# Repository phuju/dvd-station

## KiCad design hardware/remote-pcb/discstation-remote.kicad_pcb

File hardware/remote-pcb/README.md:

# DiscStation Remote PCB (r1)

One 72 × 64 mm, 2-layer board that replaces the module-based remote. It has the
same outline, mounting holes and front-panel layout as the EasyEDA carrier board.
The GPIOs are unchanged, so the firmware and host need no changes. The design notes
are in [`docs/PCB.md`](../../docs/PCB.md).

| File | What it is |
|---|---|
| `discstation-remote-schematic.pdf` | Schematic, for review |
| `discstation-remote-gerbers.zip` | Gerbers + drill files to upload to JLCPCB |
| `fab/discstation-remote-bom.csv` | Bill of materials |
| `fab/discstation-remote-pos.csv` | Pick-and-place positions (top and bottom) |
| `preview-top.png`, `preview-bottom.png` | 3D renders |
| `discstation-remote.kicad_pro/.kicad_sch/.kicad_pcb` | KiCad 10 project |

- **Front:** PLAY, HOME and EJECT Cherry MX-style key switches (3- or 5-pin), the EC11 encoder, a 4-pin OLED
  header with 4 M2 standoff holes, the power and charge LEDs.
- **Back:** ESP32-WROOM-32E (antenna on the right edge, no copper under it),
  CP2102N with DevKit-style auto-program, MCP73831 charger with a power path,
  AP2112K 3.3 V regulator, USB-C and power switch on the bottom edge, JST-PH battery
  connector (bottom-left), RESET and BOOT buttons, and the always-on eye LED (D4,
  XL-1608UBC-04) at (55.6, 58.4) mm. The 22 × 13 mm area around D4 is kept free for the
  eye/logo silkscreen art; import it with KiCad's Image Converter onto B.Silkscreen.
- LEDs are XL-1608UBC-04 (0603 blue): D2 power and D3 charging on the front, D4 eye on the back.

## Art and test pads

- **Front:** the disc sketch and "DISCSTATION" in the Phuju font, bottom-right.
- **Back:** the eye sketch, with its pupil on the eye LED (D4).
- **Test pads:** TP1 is a heart-shaped GND pad at (32.5, 9.0) mm and TP2 is a round 3V3
  pad at (69.0, 54.0) mm. Both have a 1 mm plated hole, so the pad is on both sides.

The sketches and text are converted to silkscreen polygons, so the font doesn't need to
be installed. Each piece of art is a group, so you can move it in KiCad as one unit.
The test-pad footprints are in the project library `discstation.pretty`.
To redo the art: `python3 art/prep_art.py`, then
`flatpak run --command=python3 org.kicad.KiCad art/add_art.py` on a board that has
no art yet.

## Editing

From r1 on, the KiCad files are edited by hand in KiCad 10: open
`discstation-remote.kicad_pro`. After editing, rerun DRC and export new Gerbers
from KiCad's Plot dialog, or run `./build.sh fab`, which regenerates the fab files
without touching the design.

**Do not run the full `./build.sh` after hand edits.** It regenerates the schematic
and board from `design.py` and overwrites them. The note in the schematic's title
block ("edit design.py") comes from that generator and no longer applies.

## Regenerating from scratch (generator, as used for r1)

```bash
FREEROUTING=/path/to/freerouting-1.9.0.jar ./build.sh
```

This runs the steps in order and stops at the first failure: firmware pin check →
schematic → ERC → netlist → placement (`gen_pcb.py`) → Freerouting (about 25 minutes)
→ ground pours → DRC with schematic parity → Gerbers, drill, BOM and positions.
`./build.sh fab` reruns only DRC and the fabrication outputs.

## State of r1

- ERC: 0 violations. DRC: 0 errors, 0 unconnected, 0 schematic-parity issues.
- Remaining warnings are silkscreen only (labels near the edge connectors, and labels
  over pads, which the fab house clips). The ESP32 footprint is reported as modified
  on purpose: see below.

## Review before ordering

- **Autorouted.** Check the USB D+/D− pair, the power traces and the ground pours.
- **Antenna keep-out:** Espressif's full keep-out (48 × 21 mm) does not fit on this
  board. Only the area under the antenna is kept clear, which is a common compromise
  on small boards. Wi-Fi range may be somewhat shorter than on the DevKit.
- **Positions come from a screenshot** of the old board (±1 mm). The encoder position
  is a guess, because the old board used a module with a header. Check every control
  against the enclosure, and allow for the USB-C port and power switch on the bottom
  edge (the switch lever sticks out about 0.5 mm).
- **Battery polarity:** pin 1 of J3 is `+`, but JST-PH battery leads are not wired
  the same way by every seller. Check before plugging one in.
- **Keycap clearance:** the keys keep your EasyEDA layout's spacing (about 18.4 mm
  between centres, against the usual 19.05 mm). Standard 1u keycaps (about 18 mm wide)
  leave only ~0.4 mm between them, so check that yours don't rub.
- **Encoder direction:** if turning the knob scrolls the wrong way, swap
  `ENC_CLK_PIN` and `ENC_DT_PIN` in the firmware.
- **The BOM has no LCSC part numbers.** Choose them when you upload to JLCPCB. Have
  the surface-mount parts (back side) assembled and hand-solder the through-hole parts.

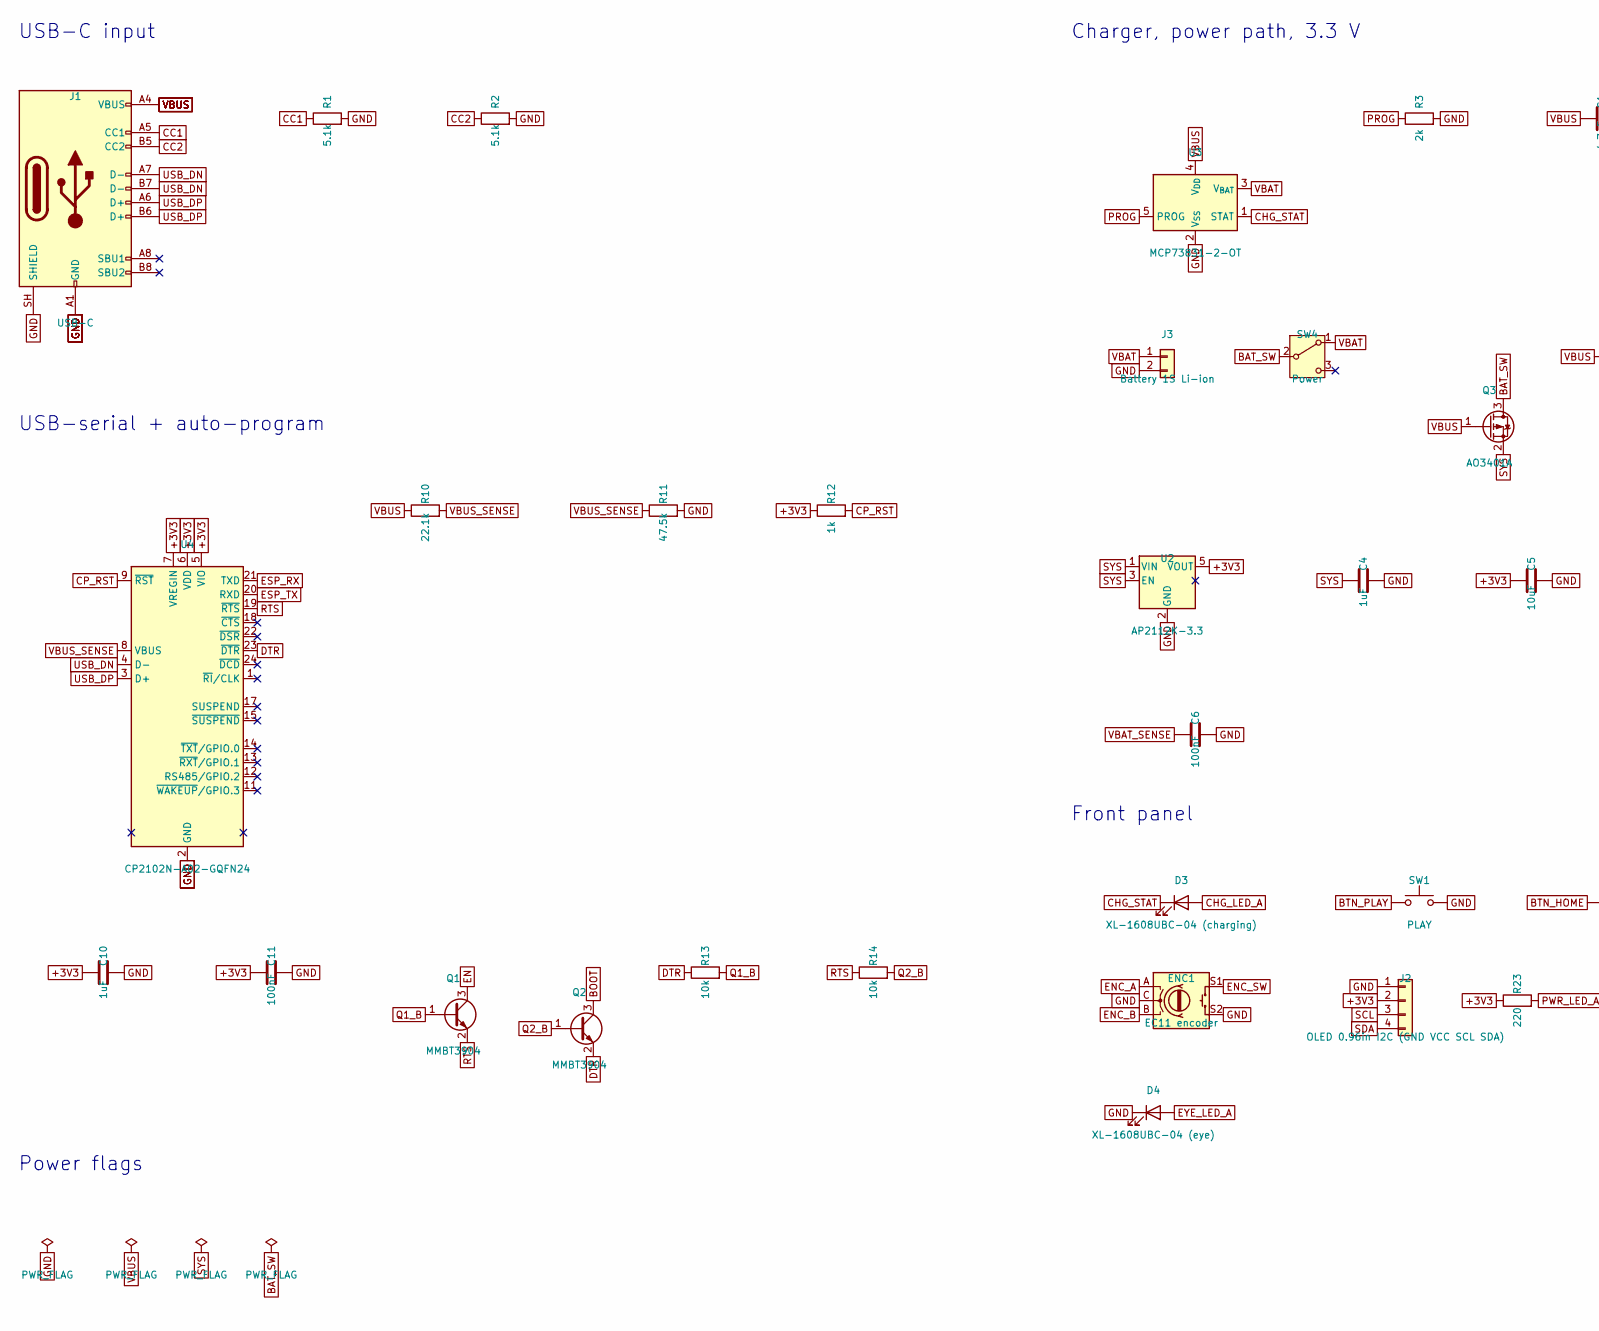
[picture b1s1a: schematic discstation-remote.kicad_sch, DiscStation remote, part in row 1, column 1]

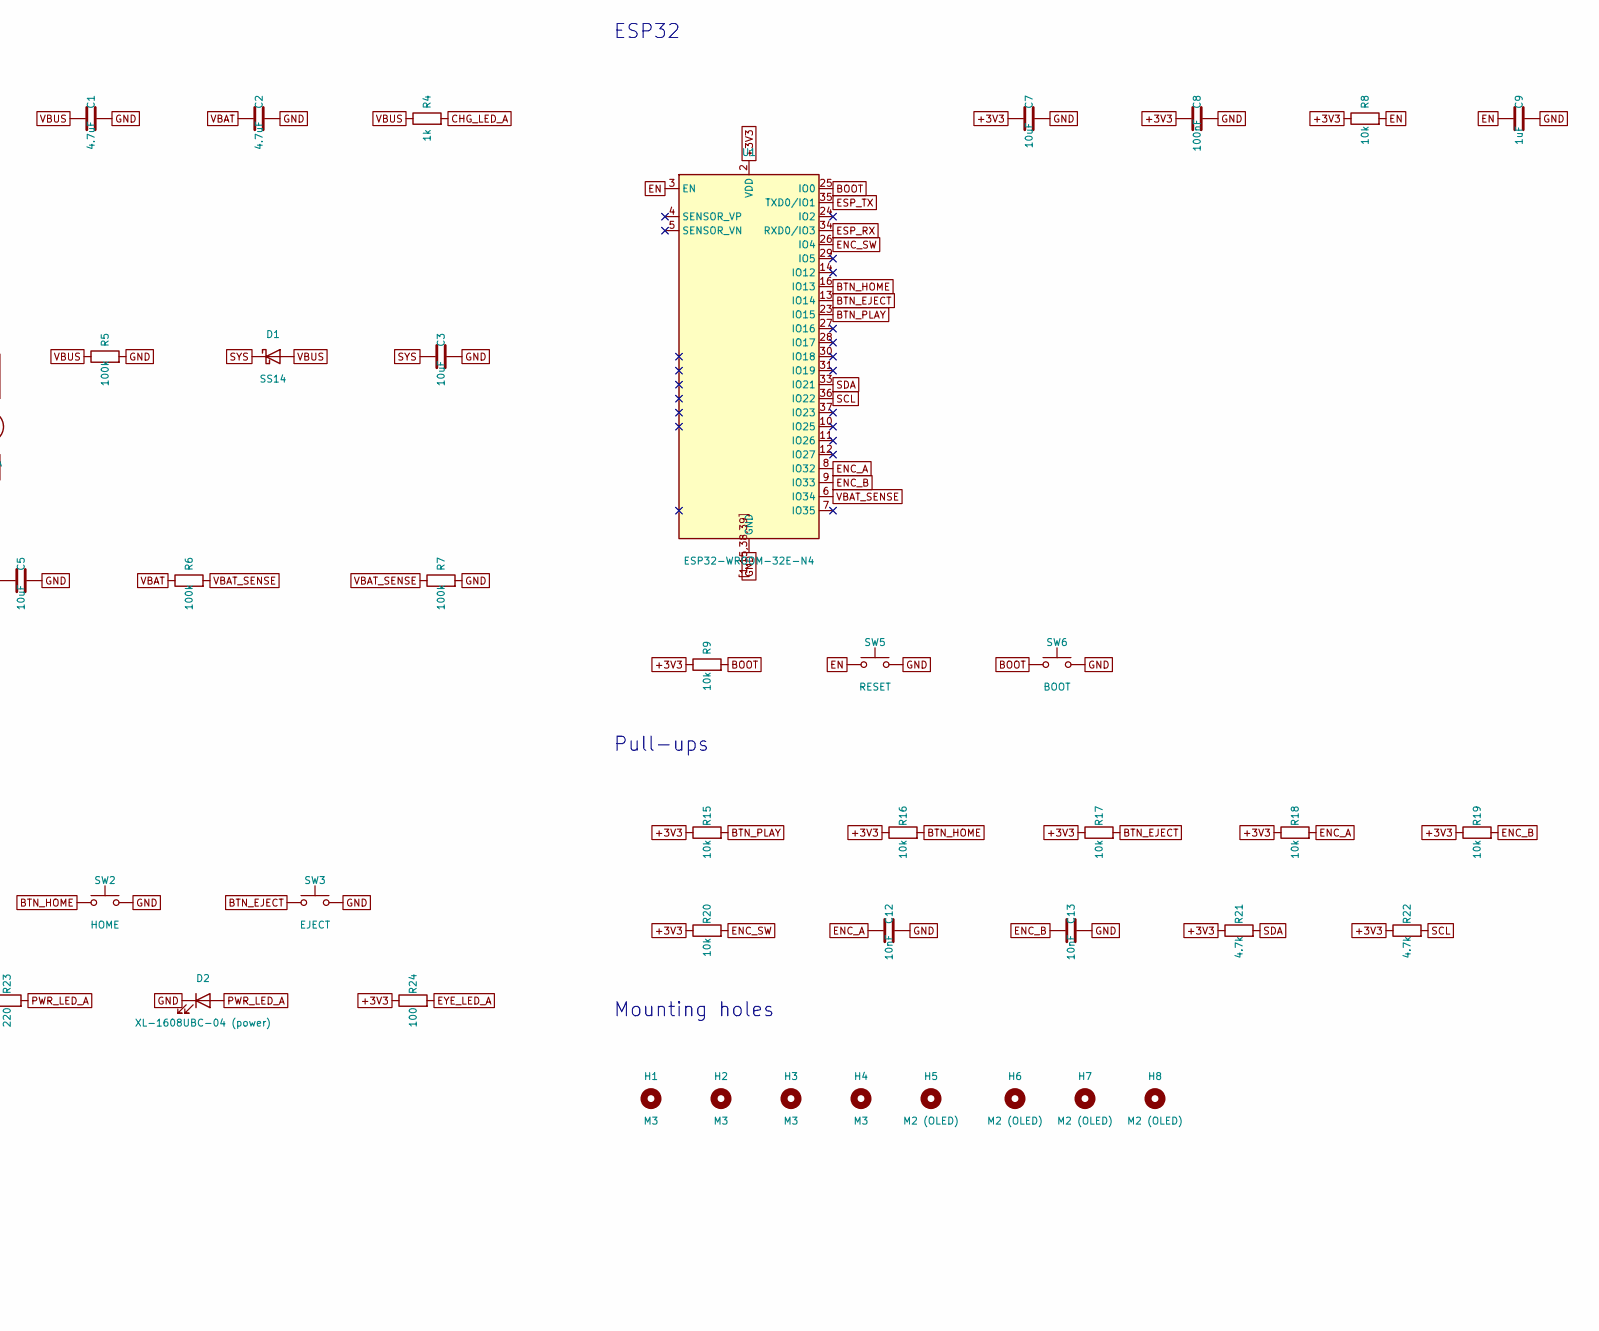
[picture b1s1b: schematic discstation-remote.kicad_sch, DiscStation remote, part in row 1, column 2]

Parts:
C1, C2: 4.7uF; C_0805_2012Metric
C3, C5, C7: 10uF; C_0805_2012Metric
C4, C9, C10: 1uF; C_0603_1608Metric
C6, C8, C11: 100nF; C_0603_1608Metric
C12, C13: 10nF; C_0603_1608Metric
D1: SS14; D_SMA
D2: XL-1608UBC-04 (power); LED_0603_1608Metric
D3: XL-1608UBC-04 (charging); LED_0603_1608Metric
D4: XL-1608UBC-04 (eye); LED_0603_1608Metric
ENC1: EC11 encoder; RotaryEncoder_Alps_EC11E-Switch_Vertical_H20mm
H1, H2, H3, H4: M3; MountingHole_3.2mm_M3
H5, H6, H7, H8: M2 (OLED); MountingHole_2.2mm_M2
J1: USB-C; USB_C_Receptacle_HRO_TYPE-C-31-M-12
J2: OLED 0.96in I2C (GND VCC SCL SDA); PinHeader_1x04_P2.54mm_Vertical
J3: Battery 1S Li-ion; JST_PH_B2B-PH-K_1x02_P2.00mm_Vertical
Q1, Q2: MMBT3904; SOT-23
Q3: AO3401A; SOT-23
R1, R2: 5.1k; R_0603_1608Metric
R3: 2k; R_0603_1608Metric
R4, R12: 1k; R_0603_1608Metric
R5, R6, R7: 100k; R_0603_1608Metric
R8, R9, R13, R14, R15, R16, R17, R18, R19, R20: 10k; R_0603_1608Metric
R10: 22.1k; R_0603_1608Metric
R11: 47.5k; R_0603_1608Metric
R21, R22: 4.7k; R_0603_1608Metric
R23: 220; R_0603_1608Metric
R24: 100; R_0603_1608Metric
SW1: PLAY; SW_Cherry_MX_1.00u_PCB
SW2: HOME; SW_Cherry_MX_1.00u_PCB
SW3: EJECT; SW_Cherry_MX_1.00u_PCB
SW4: Power; SW_SPDT_PCM12
SW5: RESET; SW_SPST_TL3342
SW6: BOOT; SW_SPST_TL3342
U1: ESP32-WROOM-32E-N4; ESP32-WROOM-32E
U2: AP2112K-3.3; SOT-23-5
U3: MCP73831-2-OT; SOT-23-5
U4: CP2102N-A02-GQFN24; QFN-24-1EP_4x4mm_P0.5mm_EP2.6x2.6mm

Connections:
+3V3: C5.1, C7.1, C8.1, C10.1, C11.1, J2.2, R8.1, R9.1, R12.1, R15.1, R16.1, R17.1, R18.1, R19.1, R20.1, R21.1, R22.1, R23.1, R24.1, U1.2 (VDD), U2.5 (VOUT), U4.5 (VIO), U4.6 (VDD), U4.7 (VREGIN); also elsewhere on the board
BAT_SW: Q3.3 (D), SW4.2 (B)
BOOT: Q2.3 (C), R9.2, SW6.1, U1.25 (IO0)
BTN_EJECT: R17.2, SW3.1, U1.13 (IO14)
BTN_HOME: R16.2, SW2.1, U1.16 (IO13)
BTN_PLAY: R15.2, SW1.1, U1.23 (IO15)
CC1: J1.A5 (CC1), R1.1
CC2: J1.B5 (CC2), R2.1
CHG_LED_A: D3.2 (A), R4.2
CHG_STAT: D3.1 (K), U3.1 (STAT)
CP_RST: R12.2, U4.9 (~RST)
DTR: Q2.2 (E), R13.1, U4.23 (~DTR)
EN: C9.1, Q1.3 (C), R8.2, SW5.1, U1.3 (EN)
ENC_A: C12.1, ENC1.A, R18.2, U1.8 (IO32)
ENC_B: C13.1, ENC1.B, R19.2, U1.9 (IO33)
ENC_SW: ENC1.S1, R20.2, U1.26 (IO4)
ESP_RX: U1.34 (RXD0/IO3), U4.21 (TXD)
ESP_TX: U1.35 (TXD0/IO1), U4.20 (RXD)
EYE_LED_A: D4.2 (A), R24.2
GND: C1.2, C2.2, C3.2, C4.2, C5.2, C6.2, C7.2, C8.2, C9.2, C10.2, C11.2, C12.2, C13.2, D2.1 (K), D4.1 (K), ENC1.C, ENC1.S2, J1.A1 (GND), J1.A12 (GND), J1.B1 (GND), J1.B12 (GND), J1.SH (SHIELD), J2.1, J3.2, R1.2, R2.2, R3.2, R5.2, R7.2, R11.2, SW1.2, SW2.2, SW3.2, SW5.2, SW6.2, U1.1, U1.15, U1.38, U1.39, U1.[1,15,38,39] (GND), U2.2 (GND), U3.2 (V_{SS}), U4.2 (GND), U4.25 (GND); also elsewhere on the board
PROG: R3.1, U3.5 (PROG)
PWR_LED_A: D2.2 (A), R23.2
Q1_B: Q1.1 (B), R13.2
Q2_B: Q2.1 (B), R14.2
RTS: Q1.2 (E), R14.1, U4.19 (~RTS)
SCL: J2.3, R22.2, U1.36 (IO22)
SDA: J2.4, R21.2, U1.33 (IO21)
SYS: C3.1, C4.1, D1.1 (K), Q3.2 (S), U2.1 (VIN), U2.3 (EN)
USB_DN: J1.A7 (D-), J1.B7 (D-), U4.4 (D-)
USB_DP: J1.A6 (D+), J1.B6 (D+), U4.3 (D+)
VBAT: C2.1, J3.1, R6.1, SW4.1 (A), U3.3 (V_{BAT})
VBAT_SENSE: C6.1, R6.2, R7.1, U1.6 (IO34)
VBUS: C1.1, D1.2 (A), J1.A4 (VBUS), J1.A9 (VBUS), J1.B4 (VBUS), J1.B9 (VBUS), Q3.1 (G), R4.1, R5.1, R10.1, U3.4 (V_{DD})
VBUS_SENSE: R10.2, R11.1, U4.8 (VBUS)

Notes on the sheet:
USB-C input
Charger, power path, 3.3 V
ESP32
USB-serial + auto-program
Pull-ups
Front panel
Mounting holes
Power flags

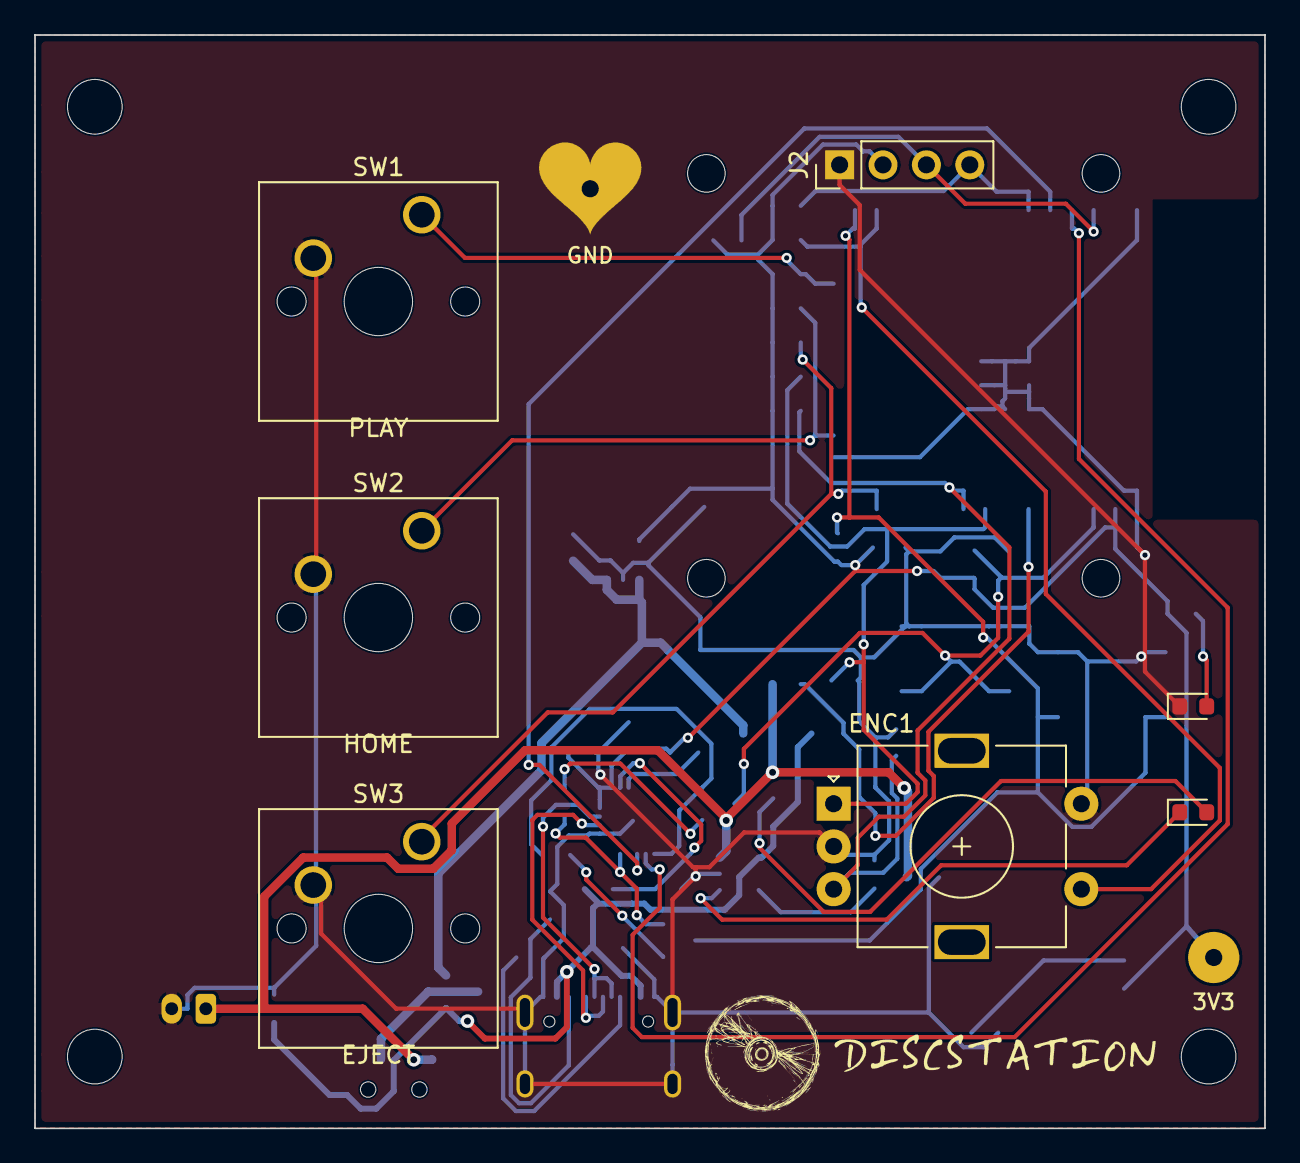
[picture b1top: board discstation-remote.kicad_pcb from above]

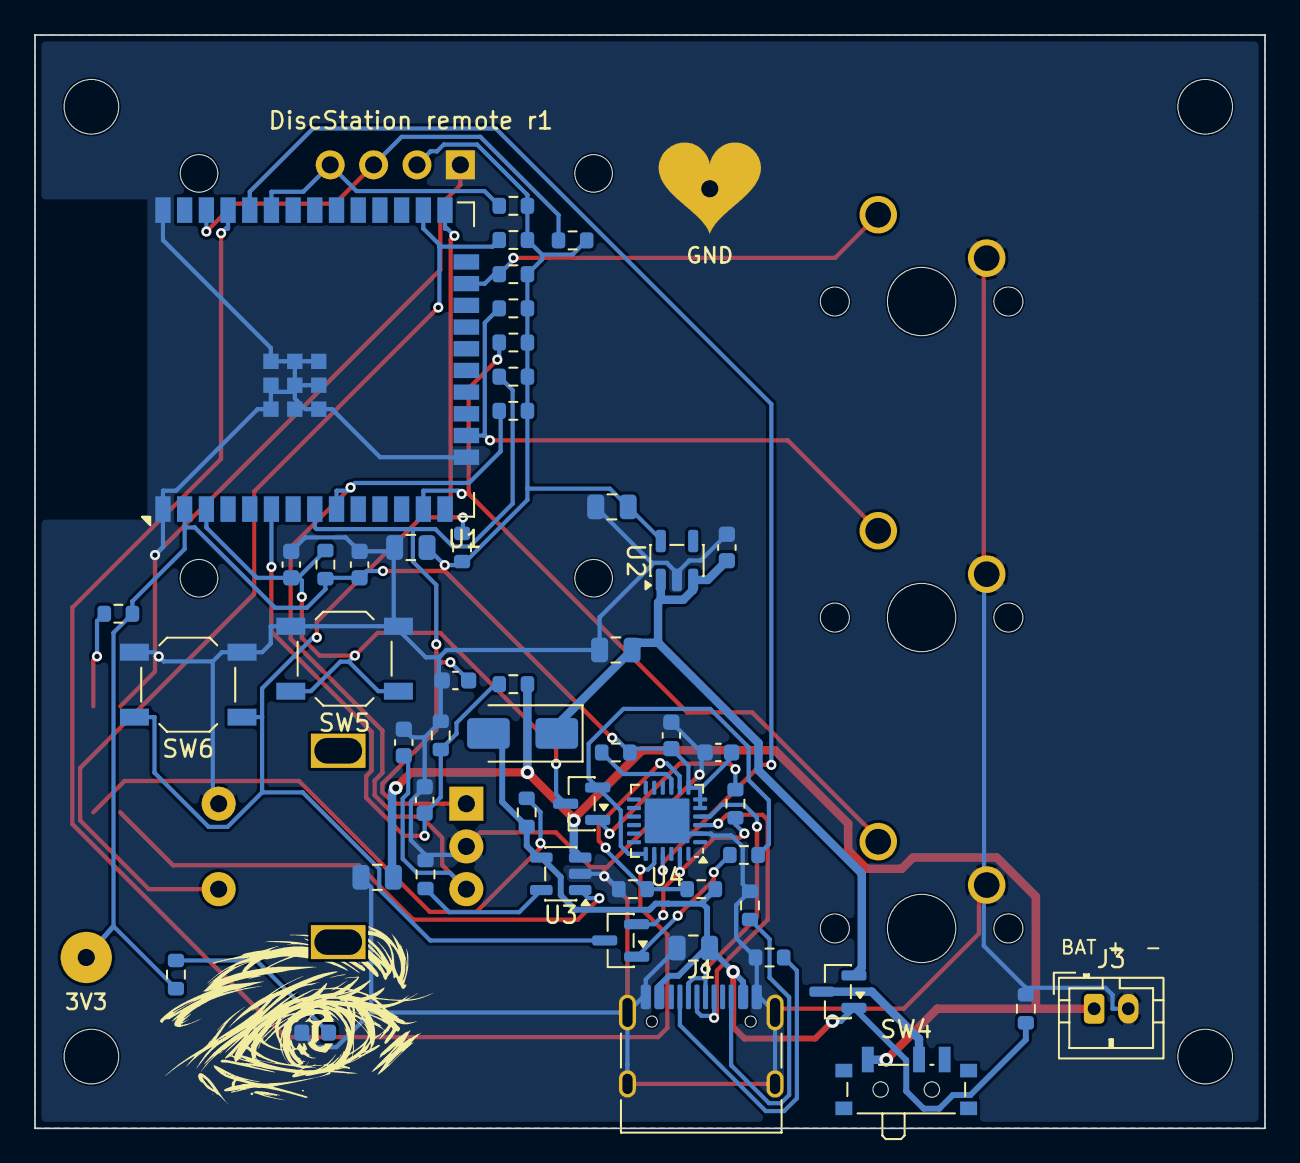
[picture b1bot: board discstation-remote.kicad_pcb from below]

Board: 2 copper layers, 72.0 x 64.0 mm, 68 parts (51 on the bottom side), 34 nets.

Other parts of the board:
TP1: GND; TestPad_Heart
TP2: +3V3; TestPad_Round

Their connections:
+3V3: TP2.1; also elsewhere on the board
GND: TP1.1; also elsewhere on the board

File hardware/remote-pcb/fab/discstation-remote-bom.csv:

"Designator","Value","Footprint","Qty"
"C1,C2","4.7uF","Capacitor_SMD:C_0805_2012Metric","2"
"C3,C5,C7","10uF","Capacitor_SMD:C_0805_2012Metric","3"
"C4,C9,C10","1uF","Capacitor_SMD:C_0603_1608Metric","3"
"C6,C8,C11","100nF","Capacitor_SMD:C_0603_1608Metric","3"
"C12,C13","10nF","Capacitor_SMD:C_0603_1608Metric","2"
"D1","SS14","Diode_SMD:D_SMA","1"
"D2","XL-1608UBC-04 (power)","LED_SMD:LED_0603_1608Metric","1"
"D3","XL-1608UBC-04 (charging)","LED_SMD:LED_0603_1608Metric","1"
"D4","XL-1608UBC-04 (eye)","LED_SMD:LED_0603_1608Metric","1"
"ENC1","EC11 encoder","Rotary_Encoder:RotaryEncoder_Alps_EC11E-Switch_Vertical_H20mm","1"
"J1","USB-C","Connector_USB:USB_C_Receptacle_HRO_TYPE-C-31-M-12","1"
"J2","OLED 0.96in I2C (GND VCC SCL SDA)","Connector_PinHeader_2.54mm:PinHeader_1x04_P2.54mm_Vertical","1"
"J3","Battery 1S Li-ion","Connector_JST:JST_PH_B2B-PH-K_1x02_P2.00mm_Vertical","1"
"Q1,Q2","MMBT3904","Package_TO_SOT_SMD:SOT-23","2"
"Q3","AO3401A","Package_TO_SOT_SMD:SOT-23","1"
"R1,R2","5.1k","Resistor_SMD:R_0603_1608Metric","2"
"R3","2k","Resistor_SMD:R_0603_1608Metric","1"
"R4,R12","1k","Resistor_SMD:R_0603_1608Metric","2"
"R5-R7","100k","Resistor_SMD:R_0603_1608Metric","3"
"R8,R9,R13-R20","10k","Resistor_SMD:R_0603_1608Metric","10"
"R10","22.1k","Resistor_SMD:R_0603_1608Metric","1"
"R11","47.5k","Resistor_SMD:R_0603_1608Metric","1"
"R21,R22","4.7k","Resistor_SMD:R_0603_1608Metric","2"
"R23","220","Resistor_SMD:R_0603_1608Metric","1"
"R24","100","Resistor_SMD:R_0603_1608Metric","1"
"SW1","PLAY","Button_Switch_Keyboard:SW_Cherry_MX_1.00u_PCB","1"
"SW2","HOME","Button_Switch_Keyboard:SW_Cherry_MX_1.00u_PCB","1"
"SW3","EJECT","Button_Switch_Keyboard:SW_Cherry_MX_1.00u_PCB","1"
"SW4","Power","Button_Switch_SMD:SW_SPDT_PCM12","1"
"SW5","RESET","Button_Switch_SMD:SW_SPST_TL3342","1"
"SW6","BOOT","Button_Switch_SMD:SW_SPST_TL3342","1"
"U1","ESP32-WROOM-32E-N4","RF_Module:ESP32-WROOM-32E","1"
"U2","AP2112K-3.3","Package_TO_SOT_SMD:SOT-23-5","1"
"U3","MCP73831-2-OT","Package_TO_SOT_SMD:SOT-23-5","1"
"U4","CP2102N-A02-GQFN24","Package_DFN_QFN:QFN-24-1EP_4x4mm_P0.5mm_EP2.6x2.6mm","1"

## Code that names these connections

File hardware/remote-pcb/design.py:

"""DiscStation remote: the one source of truth for the schematic and the PCB.

GPIOs match arduino/DiscStation/DiscStation.ino exactly (no firmware change).
Each part: ref -> (lib_id, value, footprint, {symbol pin number: net}, block).
Unlisted pins of a part are no-connects.
"""

R0603 = "Resistor_SMD:R_0603_1608Metric"
C0603 = "Capacitor_SMD:C_0603_1608Metric"
C0805 = "Capacitor_SMD:C_0805_2012Metric"
SOT23 = "Package_TO_SOT_SMD:SOT-23"
SOT235 = "Package_TO_SOT_SMD:SOT-23-5"

PARTS = {}


def part(ref, lib_id, value, fp, pins, block):
    assert ref not in PARTS, ref
    PARTS[ref] = (lib_id, value, fp, pins, block)


def R(ref, value, a, b, block):
    part(ref, "Device:R", value, R0603, {"1": a, "2": b}, block)


def C(ref, value, a, b, block, fp=C0603):
    part(ref, "Device:C", value, fp, {"1": a, "2": b}, block)


# ---- USB-C input -------------------------------------------------------------
USB_VBUS = ["A4", "A9", "B4", "B9"]
USB_GND = ["A1", "B1", "A12", "B12", "SH"]
part("J1", "Connector:USB_C_Receptacle_USB2.0_16P", "USB-C", "Connector_USB:USB_C_Receptacle_HRO_TYPE-C-31-M-12",
     {**{p: "VBUS" for p in USB_VBUS}, **{p: "GND" for p in USB_GND},
      "A5": "CC1", "B5": "CC2", "A6": "USB_DP", "B6": "USB_DP", "A7": "USB_DN", "B7": "USB_DN"}, "usb")
R("R1", "5.1k", "CC1", "GND", "usb")
R("R2", "5.1k", "CC2", "GND", "usb")

# ---- Li-ion charger + power path ------------------------------------------------
part("U3", "Battery_Management:MCP73831-2-OT", "MCP73831-2-OT", SOT235,
     {"1": "CHG_STAT", "2": "GND", "3": "VBAT", "4": "VBUS", "5": "PROG"}, "power")
R("R3", "2k", "PROG", "GND", "power")                # charge current 1000/2k = 500 mA
C("C1", "4.7uF", "VBUS", "GND", "power", C0805)
C("C2", "4.7uF", "VBAT", "GND", "power", C0805)
R("R4", "1k", "VBUS", "CHG_LED_A", "power")
part("D3", "Device:LED", "XL-1608UBC-04 (charging)", "LED_SMD:LED_0603_1608Metric", {"1": "CHG_STAT", "2": "CHG_LED_A"}, "front")
part("J3", "Connector_Generic:Conn_01x02", "Battery 1S Li-ion", "Connector_JST:JST_PH_B2B-PH-K_1x02_P2.00mm_Vertical",
     {"1": "VBAT", "2": "GND"}, "power")
part("SW4", "Switch:SW_SPDT", "Power", "Button_Switch_SMD:SW_SPDT_PCM12",
     {"1": "VBAT", "2": "BAT_SW"}, "power")
# USB present: gate high, P-FET off, load runs from VBUS via D1. USB absent:
# R5 pulls the gate low and the battery feeds SYS through the FET.
part("Q3", "Transistor_FET:AO3401A", "AO3401A", SOT23, {"1": "VBUS", "2": "SYS", "3": "BAT_SW"}, "power")
R("R5", "100k", "VBUS", "GND", "power")
part("D1", "Diode:SS14", "SS14", "Diode_SMD:D_SMA", {"1": "SYS", "2": "VBUS"}, "power")
C("C3", "10uF", "SYS", "GND", "power", C0805)

# ---- 3.3 V regulator ---------------------------------------------------------
part("U2", "Regulator_Linear:AP2112K-3.3", "AP2112K-3.3", SOT235,
     {"1": "SYS", "2": "GND", "3": "SYS", "5": "+3V3"}, "power")
C("C4", "1uF", "SYS", "GND", "power")
C("C5", "10uF", "+3V3", "GND", "power", C0805)

# battery gauge for later firmware use (GPIO34, ADC1)
R("R6", "100k", "VBAT", "VBAT_SENSE", "power")
R("R7", "100k", "VBAT_SENSE", "GND", "power")
C("C6", "100nF", "VBAT_SENSE", "GND", "power")

# ---- ESP32 ---------------------------------------------------------------------
part("U1", "RF_Module:ESP32-WROOM-32E", "ESP32-WROOM-32E-N4", "RF_Module:ESP32-WROOM-32E",
     {"[1,15,38,39]": "GND", "2": "+3V3", "3": "EN", "25": "BOOT",
      "26": "ENC_SW",       # IO4
      "16": "BTN_HOME",     # IO13
      "13": "BTN_EJECT",    # IO14
      "23": "BTN_PLAY",     # IO15 (strapping pin, idles high)
      "33": "SDA",          # IO21
      "36": "SCL",          # IO22
      "8": "ENC_A",         # IO32
      "9": "ENC_B",         # IO33
      "6": "VBAT_SENSE",    # IO34
      "35": "ESP_TX", "34": "ESP_RX"}, "mcu")
C("C7", "10uF", "+3V3", "GND", "mcu", C0805)
C("C8", "100nF", "+3V3", "GND", "mcu")
R("R8", "10k", "+3V3", "EN", "mcu")
C("C9", "1uF", "EN", "GND", "mcu")
R("R9", "10k", "+3V3", "BOOT", "mcu")
part("SW5", "Switch:SW_Push", "RESET", "Button_Switch_SMD:SW_SPST_TL3342", {"1": "EN", "2": "GND"}, "mcu")
part("SW6", "Switch:SW_Push", "BOOT", "Button_Switch_SMD:SW_SPST_TL3342", {"1": "BOOT", "2": "GND"}, "mcu")

# ---- USB-serial (CP2102N, self-powered from 3V3; VBUS sensed via divider) --------
part("U4", "Interface_USB:CP2102N-Axx-xQFN24", "CP2102N-A02-GQFN24", "Package_DFN_QFN:QFN-24-1EP_4x4mm_P0.5mm_EP2.6x2.6mm",
     {"2": "GND", "25": "GND", "3": "USB_DP", "4": "USB_DN", "5": "+3V3", "6": "+3V3", "7": "+3V3",
      "8": "VBUS_SENSE", "9": "CP_RST", "20": "ESP_TX", "21": "ESP_RX", "19": "RTS", "23": "DTR"}, "usbserial")
R("R10", "22.1k", "VBUS", "VBUS_SENSE", "usbserial")
R("R11", "47.5k", "VBUS_SENSE", "GND", "usbserial")
R("R12", "1k", "+3V3", "CP_RST", "usbserial")
C("C10", "1uF", "+3V3", "GND", "usbserial")
C("C11", "100nF", "+3V3", "GND", "usbserial")
# auto-program (same as the DevKit): DTR/RTS drive EN and IO0
part("Q1", "Transistor_BJT:MMBT3904", "MMBT3904", SOT23, {"1": "Q1_B", "2": "RTS", "3": "EN"}, "usbserial")
part("Q2", "Transistor_BJT:MMBT3904", "MMBT3904", SOT23, {"1": "Q2_B", "2": "DTR", "3": "BOOT"}, "usbserial")
R("R13", "10k", "DTR", "Q1_B", "usbserial")
R("R14", "10k", "RTS", "Q2_B", "usbserial")

# ---- controls (front) -------------------------------------------------------------
for ref, net in (("SW1", "BTN_PLAY"), ("SW2", "BTN_HOME"), ("SW3", "BTN_EJECT")):
    # Cherry MX-style key switch; the PCB-mount footprint also takes 3-pin (plate) switches
    part(ref, "Switch:SW_Push", net.split("_")[1], "Button_Switch_Keyboard:SW_Cherry_MX_1.00u_PCB", {"1": net, "2": "GND"}, "front")
part("ENC1", "Device:RotaryEncoder_Switch", "EC11 encoder", "Rotary_Encoder:RotaryEncoder_Alps_EC11E-Switch_Vertical_H20mm",
     {"A": "ENC_A", "B": "ENC_B", "C": "GND", "S1": "ENC_SW", "S2": "GND"}, "front")
for i, net in enumerate(("BTN_PLAY", "BTN_HOME", "BTN_EJECT", "ENC_A", "ENC_B", "ENC_SW"), start=15):
    R(f"R{i}", "10k", "+3V3", net, "controls")
C("C12", "10nF", "ENC_A", "GND", "controls")
C("C13", "10nF", "ENC_B", "GND", "controls")
R("R21", "4.7k", "+3V3", "SDA", "controls")
R("R22", "4.7k", "+3V3", "SCL", "controls")
part("J2", "Connector_Generic:Conn_01x04", "OLED 0.96in I2C (GND VCC SCL SDA)", "Connector_PinHeader_2.54mm:PinHeader_1x04_P2.54mm_Vertical",
     {"1": "GND", "2": "+3V3", "3": "SCL", "4": "SDA"}, "front")
R("R23", "220", "+3V3", "PWR_LED_A", "front")
part("D2", "Device:LED", "XL-1608UBC-04 (power)", "LED_SMD:LED_0603_1608Metric", {"1": "GND", "2": "PWR_LED_A"}, "front")
# decorative: lights the eye artwork on the back, always on while powered (~5 mA; lower R24 for brighter)
R("R24", "100", "+3V3", "EYE_LED_A", "front")
part("D4", "Device:LED", "XL-1608UBC-04 (eye)", "LED_SMD:LED_0603_1608Metric", {"1": "GND", "2": "EYE_LED_A"}, "front")

# ---- mechanical ---------------------------------------------------------------------
for i in range(1, 5):
    part(f"H{i}", "Mechanical:MountingHole", "M3", "MountingHole:MountingHole_3.2mm_M3", {}, "mech")
for i in range(5, 9):
    part(f"H{i}", "Mechanical:MountingHole", "M2 (OLED)", "MountingHole:MountingHole_2.2mm_M2", {}, "mech")

# Nets that need a PWR_FLAG in the schematic (driven only by passives).
PWR_FLAGS = ["GND", "VBUS", "SYS", "BAT_SW"]

# GPIO contract with the firmware: (#define name, GPIO, net)
FIRMWARE_PINS = {"BTN_EJECT_PIN": "BTN_EJECT", "BTN_HOME_PIN": "BTN_HOME", "BTN_PLAYPAUSE_PIN": "BTN_PLAY",
                 "ENC_CLK_PIN": "ENC_A", "ENC_DT_PIN": "ENC_B", "ENC_SW_PIN": "ENC_SW"}
ESP32_GPIO_PIN = {"IO4": "26", "IO13": "16", "IO14": "13", "IO15": "23", "IO21": "33", "IO22": "36", "IO32": "8", "IO33": "9"}


def nets():
    out = {}
    for ref, (_, _, _, pins, _) in PARTS.items():
        for pin, net in pins.items():
            out.setdefault(net, []).append((ref, pin))
    return out


if __name__ == "__main__":
    import re
    from pathlib import Path
    n = nets()
    # every net needs at least two connections
    lonely = {k: v for k, v in n.items() if len(v) < 2}
    assert not lonely, lonely
    # firmware pin contract
    ino = (Path(__file__).resolve().parents[2] / "arduino/DiscStation/DiscStation.ino").read_text()
    u1 = PARTS["U1"][3]
    for define, net in FIRMWARE_PINS.items():
        gpio = int(re.search(rf"#define {define}\s+(\d+)", ino).group(1))
        assert u1[ESP32_GPIO_PIN[f"IO{gpio}"]] == net, (define, gpio, net)
    assert u1[ESP32_GPIO_PIN["IO21"]] == "SDA" and u1[ESP32_GPIO_PIN["IO22"]] == "SCL"
    print(f"{len(PARTS)} parts, {len(n)} nets; firmware GPIO contract OK")
